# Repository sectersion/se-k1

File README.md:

# Secure Element K1

This project is a small hardware password vault and crypto cold wallet using an ESP32-S3, a TPM (SLB9670), and a W25Q-series SPI flash chip.  

I created this project because a family member was talking about crypto wallets, and it gave me the idea of password managers. Online password managers are tied to one login and if that gets breached, all your accounts are gone. This implements a secure way to hold passwords, fully offline, not relying on cloud providers like Google.

## Features

- ESP32-S3 with USB HID keyboard output  
- TPM-backed master key for decrypting stored passwords  
- External SPI flash for record storage (ID, encrypted password, hashed PIN, MAC)  
- Button-based keypad input  
- PIN verification using SHA-256 with device-unique salt  
- Short-lived in-memory plaintext handling

## System

1. User enters a 4-digit record ID.  
2. Device loads the corresponding record from flash.  
3. User enters a 6-digit PIN.  
4. PIN is hashed and compared to the stored hash.  
5. If valid, the TPM unseals the master key.  
6. The encrypted password is decrypted using the TPM-provided key.  
7. The password is typed over USB HID.  
8. Plaintext is cleared.

## Components

| Designator | Footprint | Quantity | Value | LCSC Part # |
|---|---|---|---|---|
| 3V3 | TestPoint_Pad_D1.0mm | 1 | 3V3 | |
| 5V | TestPoint_Pad_D1.0mm | 1 | 5V | |
| BT1 | BatteryHolder_Renata_SMTU2032-LF_1x2032 | 1 | SMTU2032-LF | C18212226 |
| C1, C3, C7 | 0402 | 3 | 10uF | C315248 |
| C2 | CP_Elec_6.3x5.8 | 1 | 10uF | C128459 |
| C4 | 0402 | 1 | 0.1uF | C60474 |
| C5, C6 | 0402 | 2 | 100nF | C60474 |
| C8 | 0805 | 1 | 100nF | C49678 |
| D1 | D_SMA | 1 | SS14 | C2837270 |
| J1 | USB_C_Receptacle_HRO_TYPE-C-31-M-12 | 1 | USB_C_Receptacle_USB2.0_14P | C2765186 |
| R1, R2 | 0402 | 2 | 5.1k | C105872 |
| R3, R4, R5, R6, R8 | 0402 | 5 | 10k | C60490 |
| RST | SW_TS-1088-AR02016 | 1 | TS-1088-AR02016 | C720477 |
| RXD | TestPoint_Pad_D1.0mm | 1 | RX | |
| S1 | SW_TS-1088-AR02016 | 1 | 1 | C720477 |
| S2 | SW_TS-1088-AR02016 | 1 | 4 | C720477 |
| S3 | SW_TS-1088-AR02016 | 1 | 7 | C720477 |
| S4 | SW_TS-1088-AR02016 | 1 | 2 | C720477 |
| S5 | SW_TS-1088-AR02016 | 1 | 5 | C720477 |
| S6 | SW_TS-1088-AR02016 | 1 | 8 | C720477 |
| S7 | SW_TS-1088-AR02016 | 1 | 3 | C720477 |
| S8 | SW_TS-1088-AR02016 | 1 | 6 | C720477 |
| S9 | SW_TS-1088-AR02016 | 1 | 9 | C720477 |
| S10 | SW_TS-1088-AR02016 | 1 | 0 | C720477 |
| TXD | TestPoint_Pad_D1.0mm | 1 | TX | |
| U1 | ESP32-S2-MINI-1U | 1 | ESP32-S3-MINI-1U | C2980299 |
| U2 | QFN50P500X500X90-33N | 1 | SLM9670AQ20FW1311XTMA1 | C2651754 |
| U3 | SOIC127P790X216-8N | 1 | W25Q16JVSSIQ | C82317 |
| U4 | SOT-223-3_TabPin2 | 1 | AMS1117-3.3 | C6186 |

## Record Format

Each stored record contains:

- id: 4 bytes  
- encrypted_password: fixed length  
- encrypted_pin: 16-byte truncated SHA-256 hash  
- mac: record integrity field

## Pictures
3D model:

PCB:

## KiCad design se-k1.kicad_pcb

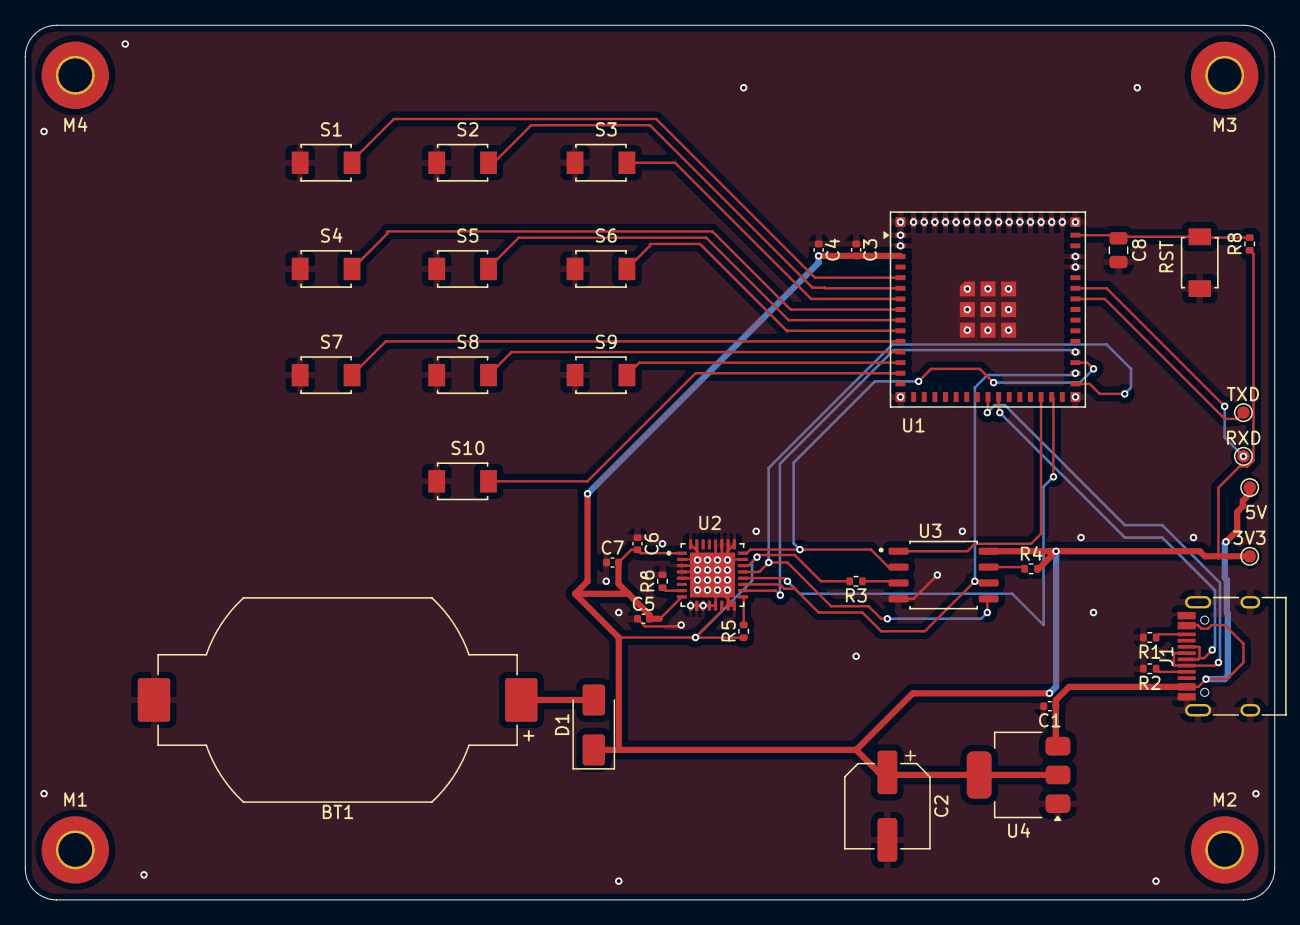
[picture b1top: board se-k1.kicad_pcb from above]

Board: 2 copper layers, 100.0 x 70.0 mm, 41 parts (0 on the bottom side), 31 nets.

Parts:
3V3: 3V3; TestPoint_Pad_D1.0mm
5V: 5V; TestPoint_Pad_D1.0mm
BT1: SMTU2032-LF; BatteryHolder_Renata_SMTU2032-LF_1x2032
C1, C3, C7: 10uF; C_0402_1005Metric
C2: 10uF; CP_Elec_6.3x5.8
C4: 0.1uF; C_0402_1005Metric
C5, C6: 100nF; C_0402_1005Metric
C8: 100nF; C_0805_2012Metric
D1: SS14; D_SMA
J1: USB_C_Receptacle_USB2.0_14P; USB_C_Receptacle_HRO_TYPE-C-31-M-12
M1, M2, M3, M4: MountingHole_2.7mm_M2.5_Pad_TopOnly
R1, R2: 5.1k; R_0402_1005Metric
R3, R4, R5, R6, R8: 10k; R_0402_1005Metric
RST: TS-1088-AR02016; SW_TS-1088-AR02016
RXD: RX; TestPoint_Pad_D1.0mm
S1: 1; SW_TS-1088-AR02016
S2: 4; SW_TS-1088-AR02016
S3: 7; SW_TS-1088-AR02016
S4: 2; SW_TS-1088-AR02016
S5: 5; SW_TS-1088-AR02016
S6: 8; SW_TS-1088-AR02016
S7: 3; SW_TS-1088-AR02016
S8: 6; SW_TS-1088-AR02016
S9: 9; SW_TS-1088-AR02016
S10: 0; SW_TS-1088-AR02016
TXD: TX; TestPoint_Pad_D1.0mm
U1: ESP32-S3-MINI-1U; ESP32-S2-MINI-1U
U2: SLM9670AQ20FW1311XTMA1; QFN50P500X500X90-33N
U3: W25Q16JVSSIQ; SOIC127P790X216-8N
U4: AMS1117-3.3; SOT-223-3_TabPin2

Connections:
+3V3: 3V3.1, C2.1, C3.2, C4.2, C5.2, C6.2, C7.2, D1.1 (K), R3.2, R4.2, R5.1, R8.1, U1.3 (3V3), U2.1 (NCI/VDD), U2.8 (VDD), U2.14 (NCI/VDD), U2.22 (VDD), U3.8 (VCC), U4.2 (VO)
+5V: 5V.1, C1.1, J1.A4 (VBUS), J1.A9 (VBUS), J1.B4 (VBUS), J1.B9 (VBUS), U4.3 (VI)
/B0: S10.2, U1.14 (IO10)
/B1: S1.2, U1.5 (IO1)
/B2: S2.2, U1.6 (IO2)
/B3: S3.2, U1.7 (IO3)
/B4: S4.B4, U1.8 (IO4)
/B5: S5.2, U1.9 (IO5)
/B6: S6.2, U1.10 (IO6)
/B7: S7.2, U1.11 (IO7)
/B8: S8.2, U1.12 (IO8)
/B9: S9.2, U1.13 (IO9)
/D+: J1.A6 (D+), J1.B6 (D+), U1.24 (USB_D+)
/D-: J1.A7 (D-), J1.B7 (D-), U1.23 (USB_D-)
/FLASH_CS: U1.28 (IO33), U3.1 (~CS)
/MISO: U1.33 (IO37), U2.24 (MISO), U3.2 (DO(IO1))
/MOSI: U1.31 (IO35), U2.21 (MOSI), U3.5 (DI(IO0))
/SCLK: U1.32 (IO36), U2.19 (SCLK), U3.6 (CLK)
/TPM_CS: U1.29 (IO34), U2.20 (~CS)
/TPM_PIRQ: U1.34 (IO38), U2.18 (~PIRQ)
GND: BT1.2, C1.2, C2.2, C3.1, C4.1, C5.1, C6.1, C7.1, C8.2, J1.A1 (GND), J1.A12 (GND), J1.B1 (GND), J1.B12 (GND), J1.S1 (SHIELD), R1.2, R2.2, R6.2, RST.1, S1.1, S2.1, S3.1, S4.1, S5.1, S6.1, S7.1, S8.1, S9.1, S10.1, U1.1 (GND), U1.2 (GND), U1.42 (GND), U1.43 (GND), U1.46 (GND), U1.47 (GND), U1.48 (GND), U1.49 (GND), U1.50 (GND), U1.51 (GND), U1.52 (GND), U1.53 (GND), U1.54 (GND), U1.55 (GND), U1.56 (GND), U1.57 (GND), U1.58 (GND), U1.59 (GND), U1.60 (GND), U1.61 (GND), U1.62 (GND), U1.63 (GND), U1.64 (GND), U1.65 (GND), U2.2 (GND), U2.3 (NCI), U2.4 (NCI), U2.5 (NCI), U2.9 (GND), U2.10 (NCI), U2.11 (NCI), U2.12 (NCI), U2.13 (NCI), U2.15 (NCI), U2.16 (NCI/GND), U2.23 (GND), U2.25 (NCI), U2.26 (NCI), U2.27 (NCI), U2.28 (NCI), U2.31 (NCI), U2.32 (GND), U2.33 (EXP), U3.4 (GND), U4.1 (GND)
unnamed: BT1.1, D1.2 (A)
unnamed: J1.A5 (CC1), R2.1
unnamed: J1.B5 (CC2), R1.1
unnamed: C8.1, R8.2, RST.2, U1.45 (EN)
unnamed: RXD.1, U1.40 (RXD0)
unnamed: TXD.1, U1.39 (TXD0)
unnamed: R6.1, U2.7 (PP)
unnamed: R5.2, U2.17 (~RST)
unnamed: R4.1, U3.7 (~HOLD/RESET(IO3))
unnamed: R3.1, U3.3 (~WP(IO2))

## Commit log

2026-03-30 upload
2026-04-05 finish!
2026-04-06 Expand README with project details and images
    Added detailed project description, features, system overview, components list, record format, and images.
